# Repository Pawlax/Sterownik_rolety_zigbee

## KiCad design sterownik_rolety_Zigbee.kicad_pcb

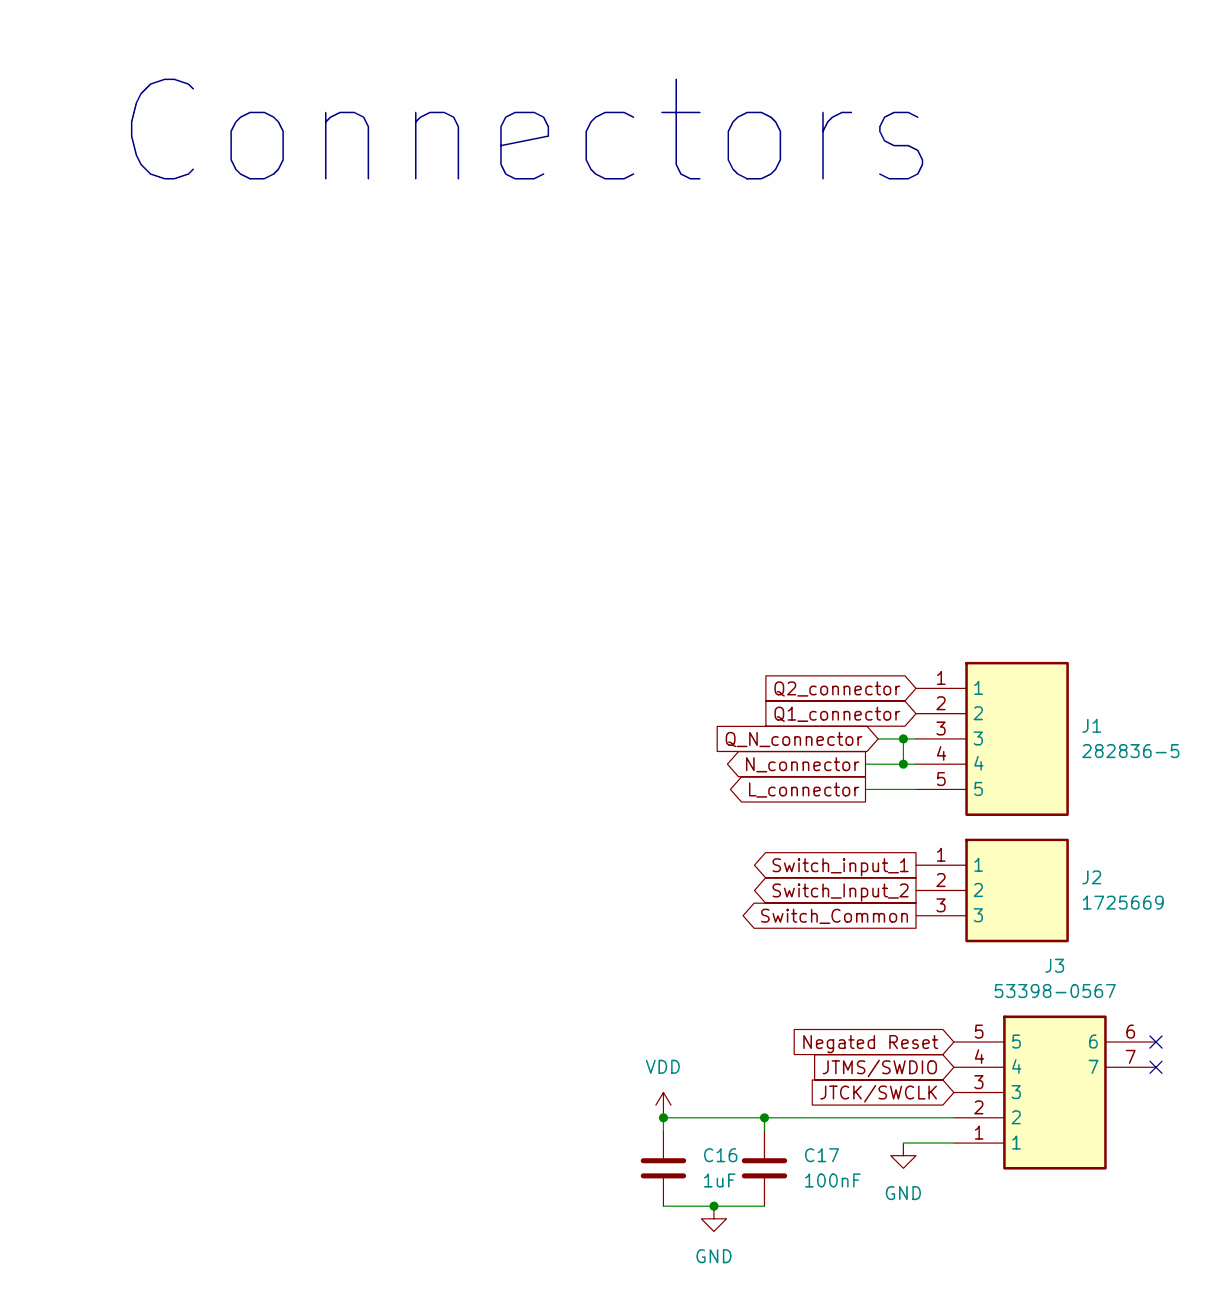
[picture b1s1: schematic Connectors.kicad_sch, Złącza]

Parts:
C16: 1uF; C_0603_1608Metric_Pad1.08x0.95mm_HandSolder
C17: 100nF; C_0603_1608Metric_Pad1.08x0.95mm_HandSolder
J1: 282836-5; 2828365; Mouser Part Number 571-2828365
J2: 1725669; Mouser Part Number 651-1725669
J3: 53398-0567; 533980567; Mouser Part Number 538-53398-0567

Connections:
GND: C16.2, C17.2, J3.1; also elsewhere on the board
JTCK/SWCLK: J3.3; also elsewhere on the board
JTMS/SWDIO: J3.4; also elsewhere on the board
L_connector: J1.5; also elsewhere on the board
N_connector: J1.3, J1.4; also elsewhere on the board
Negated Reset: J3.5; also elsewhere on the board
Q1_connector: J1.2; also elsewhere on the board
Q2_connector: J1.1; also elsewhere on the board
Switch_Common: J2.3; also elsewhere on the board
Switch_Input_2: J2.2; also elsewhere on the board
Switch_input_1: J2.1; also elsewhere on the board
VDD: C16.1, C17.1, J3.2; also elsewhere on the board

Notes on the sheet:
Connectors

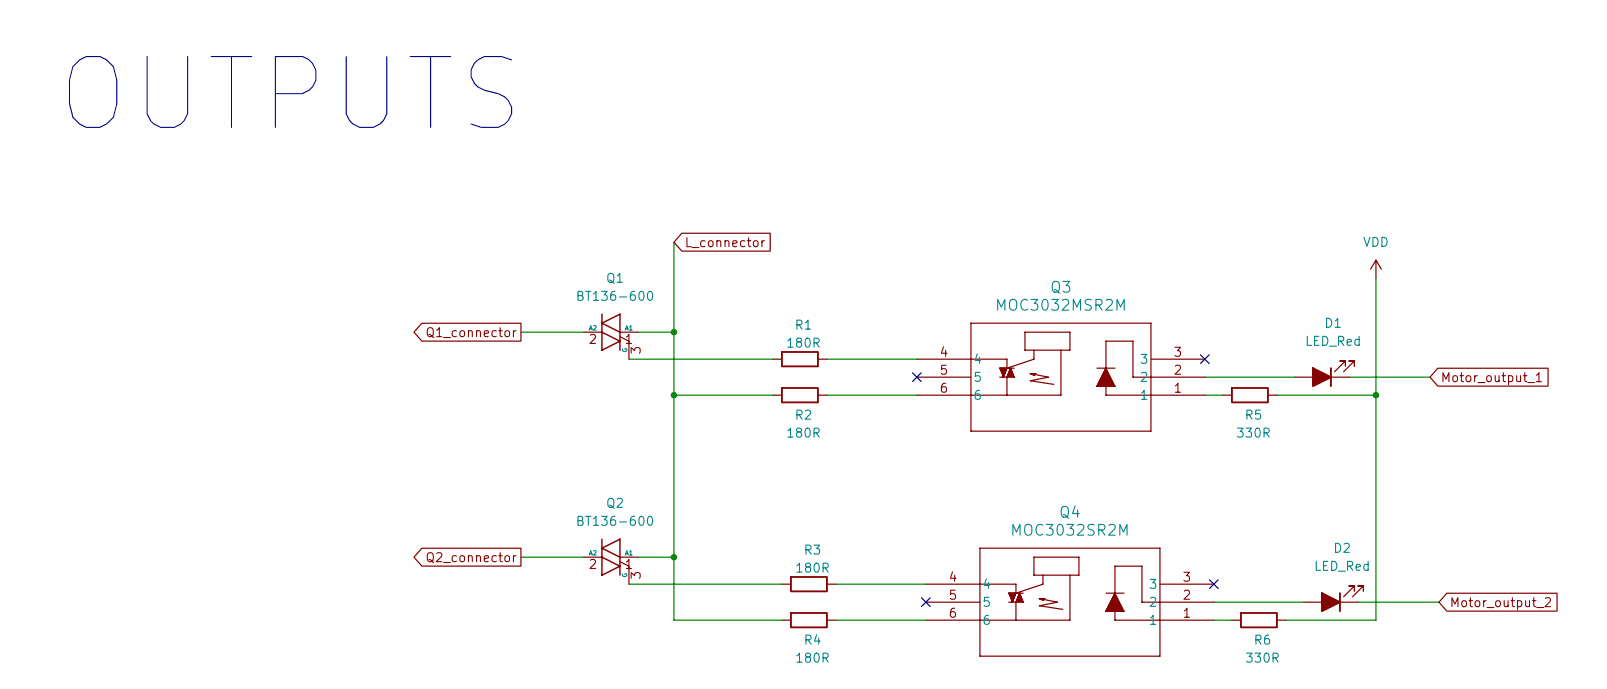
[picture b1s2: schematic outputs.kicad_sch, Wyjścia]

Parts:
D1, D2: LED_Red; LED_0603_1608Metric_Pad1.05x0.95mm_HandSolder
Q1, Q2: BT136-600; TO-220-3_Vertical
Q3: MOC3032MSR2M; DIP-6_W8.89mm_SMDSocket_LongPads
Q4: MOC3032SR2M; DIP-6_W8.89mm_SMDSocket_LongPads
R1, R2, R3, R4: 180R; R_0603_1608Metric_Pad0.98x0.95mm_HandSolder
R5, R6: 330R; R_0603_1608Metric_Pad0.98x0.95mm_HandSolder

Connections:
L_connector: Q1.1 (A1), Q2.1 (A1), R2.2, R4.2; also elsewhere on the board
Motor_output_1: D1.1 (K); also elsewhere on the board
Motor_output_2: D2.1 (K); also elsewhere on the board
unnamed: D1.2 (A), Q3.2
unnamed: D2.2 (A), Q4.2
unnamed: Q1.3 (G), R1.2
unnamed: Q2.3 (G), R3.2
unnamed: Q3.1, R5.2
unnamed: Q3.4, R1.1
unnamed: Q3.6, R2.1
unnamed: Q4.1, R6.2
unnamed: Q4.4, R3.1
unnamed: Q4.6, R4.1
Q1_connector: Q1.2 (A2); also elsewhere on the board
Q2_connector: Q2.2 (A2); also elsewhere on the board
VDD: R5.1, R6.1; also elsewhere on the board

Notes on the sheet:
OUTPUTS

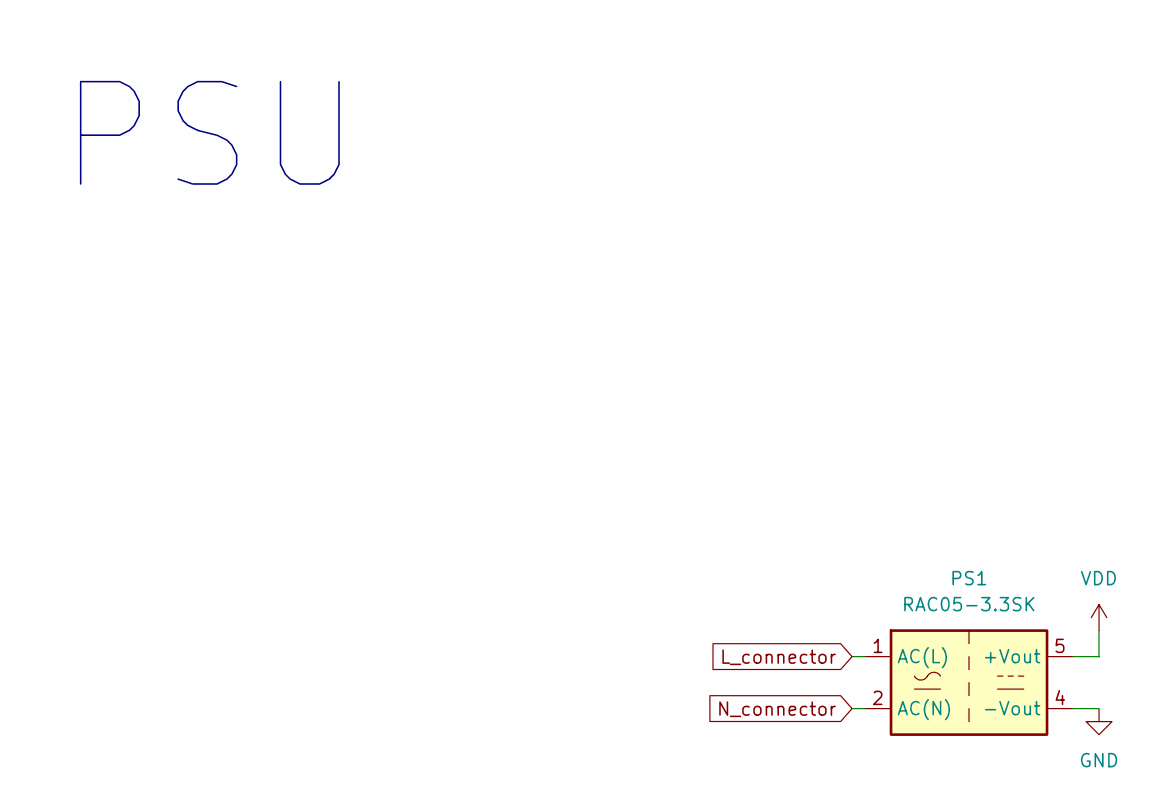
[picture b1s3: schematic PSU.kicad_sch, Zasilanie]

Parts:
PS1: RAC05-3.3SK; Converter_ACDC_RECOM_RAC05-xxSK_THT

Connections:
GND: PS1.4 (-Vout); also elsewhere on the board
L_connector: PS1.1 (AC(L)); also elsewhere on the board
N_connector: PS1.2 (AC(N)); also elsewhere on the board
VDD: PS1.5 (+Vout); also elsewhere on the board

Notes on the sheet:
PSU

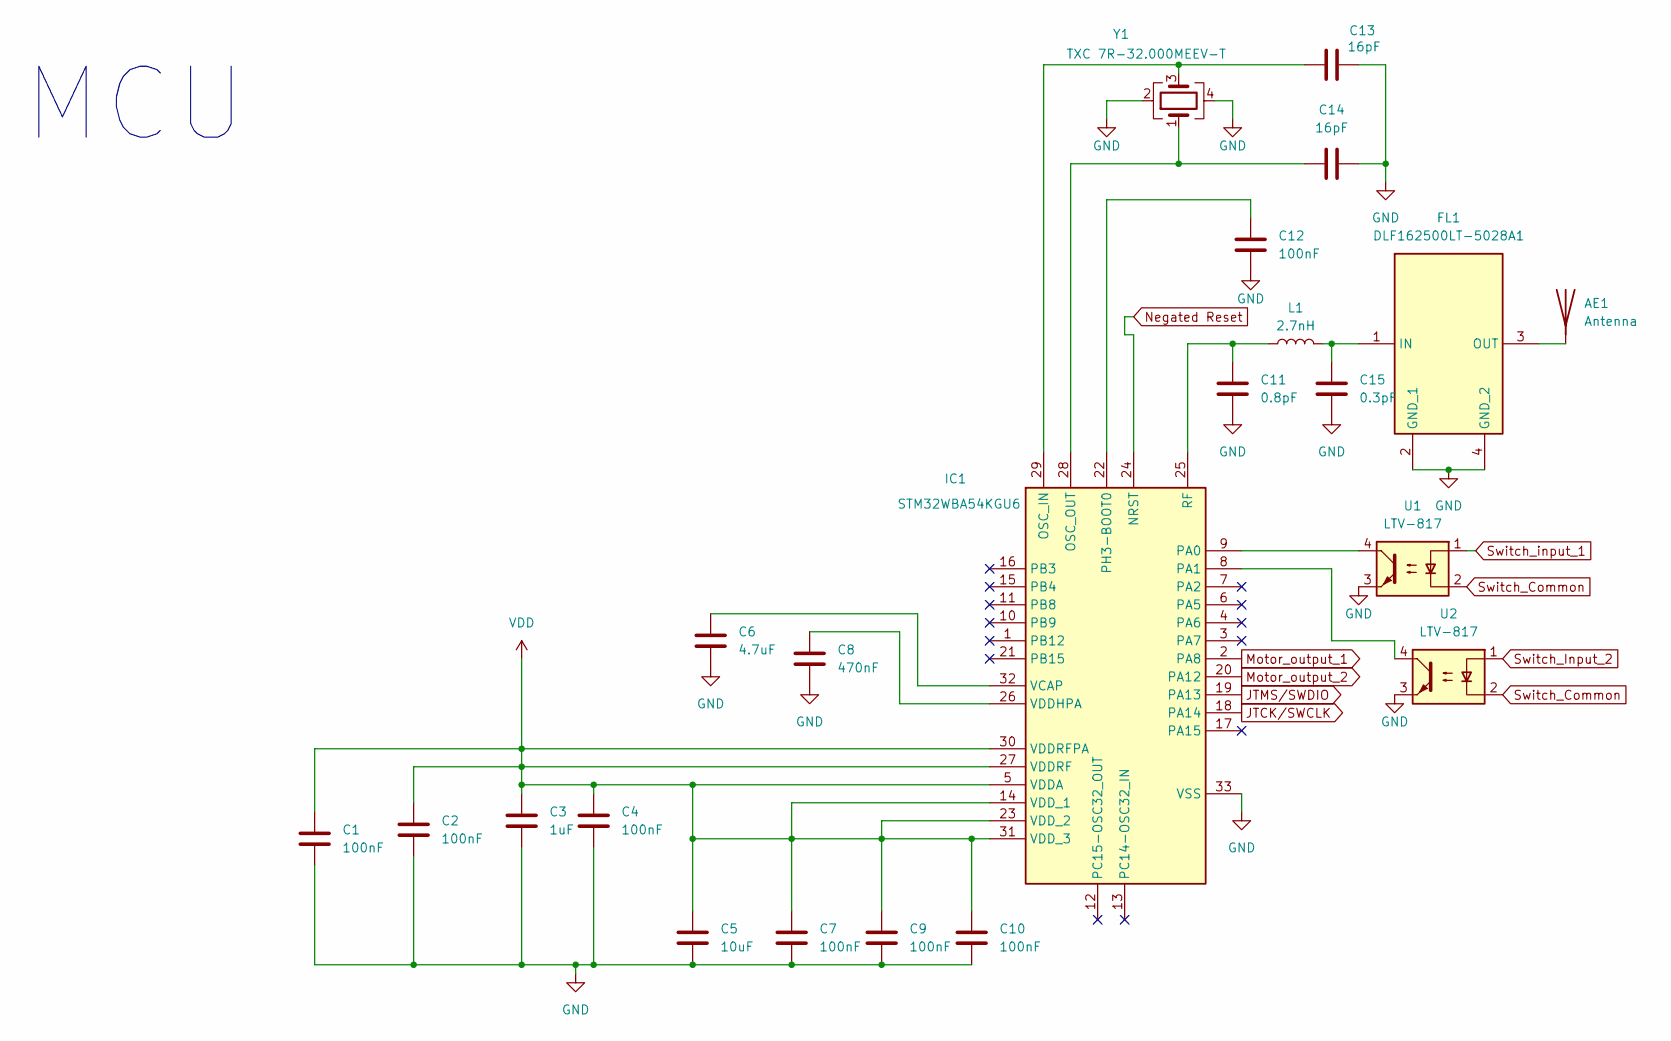
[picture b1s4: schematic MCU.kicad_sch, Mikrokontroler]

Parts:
AE1: Antenna; Texas_SWRA117D_2.4GHz_Right
C1, C2, C4, C7, C9, C10, C12: 100nF; C_0603_1608Metric_Pad1.08x0.95mm_HandSolder
C3: 1uF; C_0603_1608Metric_Pad1.08x0.95mm_HandSolder
C5: 10uF; C_0603_1608Metric_Pad1.08x0.95mm_HandSolder
C6: 4.7uF; C_0603_1608Metric_Pad1.08x0.95mm_HandSolder
C8: 470nF; C_0603_1608Metric_Pad1.08x0.95mm_HandSolder
C11: 0.8pF; C_0603_1608Metric_Pad1.08x0.95mm_HandSolder
C13, C14: 16pF; C_0603_1608Metric_Pad1.08x0.95mm_HandSolder
C15: 0.3pF; C_0603_1608Metric_Pad1.08x0.95mm_HandSolder
FL1: DLF162500LT-5028A1; DLF162500LT5028A1; Mouser Part Number 810-DLF16250LT5028A1
IC1: STM32WBA54KGU6; QFN50P500X500X60-33N-D; Mouser Part Number 511-STM32WBA54KGU6
L1: 2.7nH; L_0603_1608Metric_Pad1.05x0.95mm_HandSolder
U1, U2: LTV-817; SMDIP-4_W9.53mm
Y1: TXC 7R-32.000MEEV-T

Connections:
GND: C1.2, C2.2, C3.2, C4.2, C5.2, C6.2, C7.2, C8.2, C9.2, C10.2, C11.2, C12.2, C13.1, C14.1, C15.2, FL1.2 (GND_1), FL1.4 (GND_2), IC1.33 (VSS), U1.3, U2.3, Y1.2, Y1.4; also elsewhere on the board
JTCK/SWCLK: IC1.18 (PA14); also elsewhere on the board
JTMS/SWDIO: IC1.19 (PA13); also elsewhere on the board
Motor_output_1: IC1.2 (PA8); also elsewhere on the board
Motor_output_2: IC1.20 (PA12); also elsewhere on the board
Negated Reset: IC1.24 (NRST); also elsewhere on the board
unnamed: AE1.1 (A), FL1.3 (OUT)
unnamed: C15.1, FL1.1 (IN), L1.2
unnamed: C13.2, IC1.29 (OSC_IN), Y1.3
unnamed: C14.2, IC1.28 (OSC_OUT), Y1.1
unnamed: IC1.9 (PA0), U1.4
unnamed: IC1.8 (PA1), U2.4
unnamed: C12.1, IC1.22 (PH3-BOOT0)
unnamed: C11.1, IC1.25 (RF), L1.1
unnamed: C6.1, IC1.32 (VCAP)
unnamed: C8.1, IC1.26 (VDDHPA)
Switch_Common: U1.2, U2.2; also elsewhere on the board
Switch_Input_2: U2.1; also elsewhere on the board
Switch_input_1: U1.1; also elsewhere on the board
VDD: C1.1, C2.1, C3.1, C4.1, C5.1, C7.1, C9.1, C10.1, IC1.5 (VDDA), IC1.14 (VDD_1), IC1.23 (VDD_2), IC1.27 (VDDRF), IC1.30 (VDDRFPA), IC1.31 (VDD_3); also elsewhere on the board

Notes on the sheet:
MCU

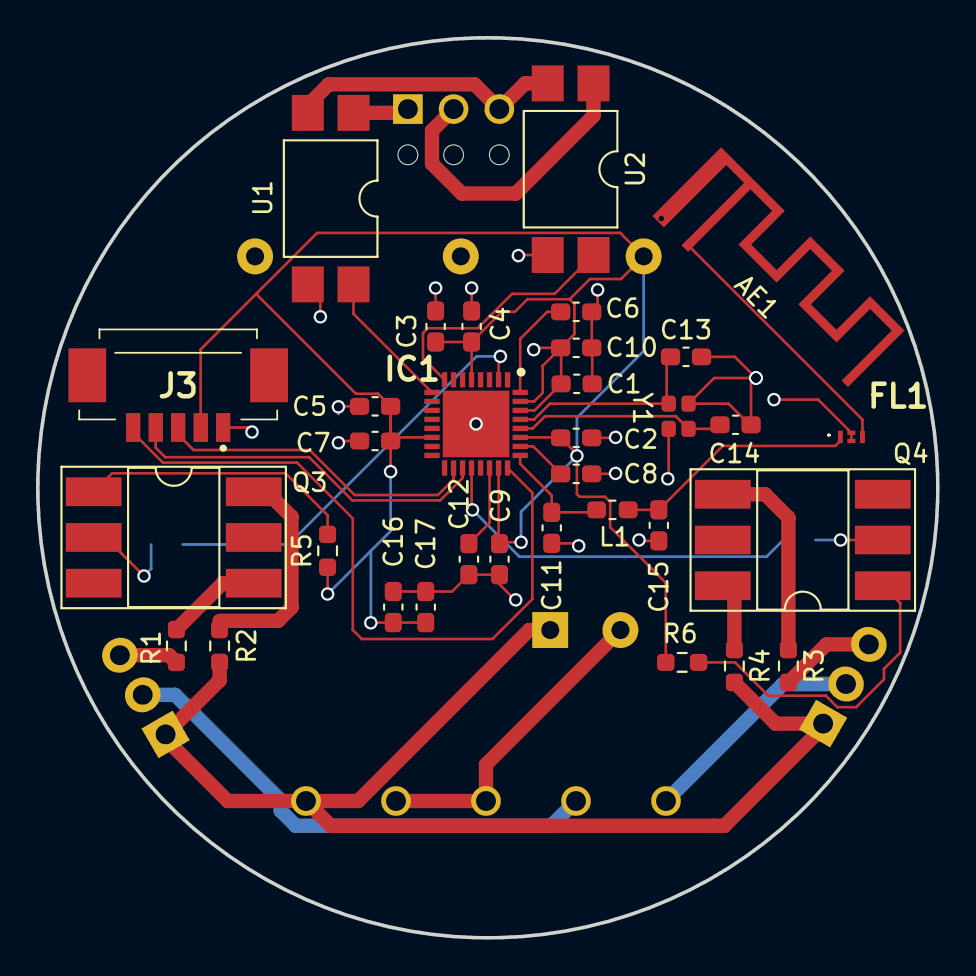
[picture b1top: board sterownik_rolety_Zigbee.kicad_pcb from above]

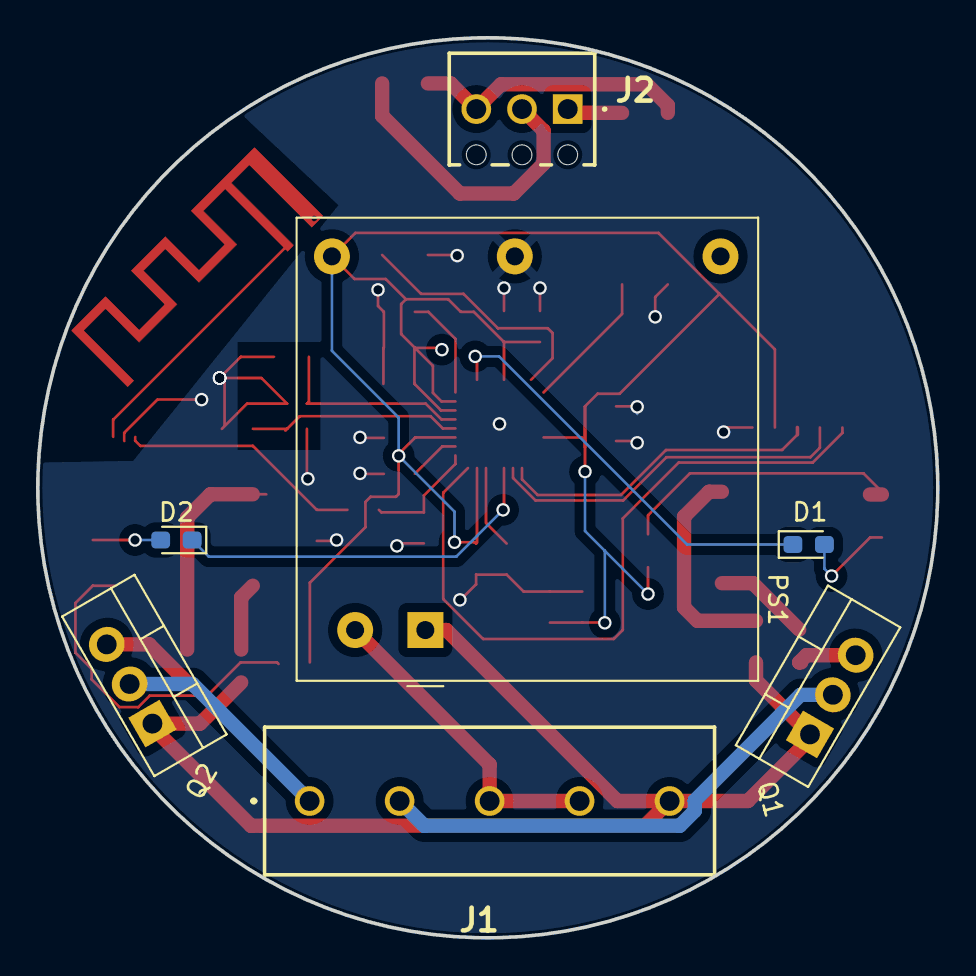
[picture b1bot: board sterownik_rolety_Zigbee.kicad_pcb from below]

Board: 2 copper layers, 50.0 x 50.0 mm, 40 parts (7 on the bottom side), 34 nets.

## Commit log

2024-12-11 kryształ kondensatory i interfejs podłączone z mikrokontrolerem
2024-12-30 połączenie ścieżkami, wylanie masy
2025-01-04 BOM Gerbery, schemat w pdfie i zip do oddania na razie bez wszystkich numerów indeksu
2025-01-05 poprawka wymiaru płytki
2025-01-05 Wersja finalna
2025-01-05 BOM Gerbery, schemat w pdfie i zip do oddanie bez jednego numeru indeksu
